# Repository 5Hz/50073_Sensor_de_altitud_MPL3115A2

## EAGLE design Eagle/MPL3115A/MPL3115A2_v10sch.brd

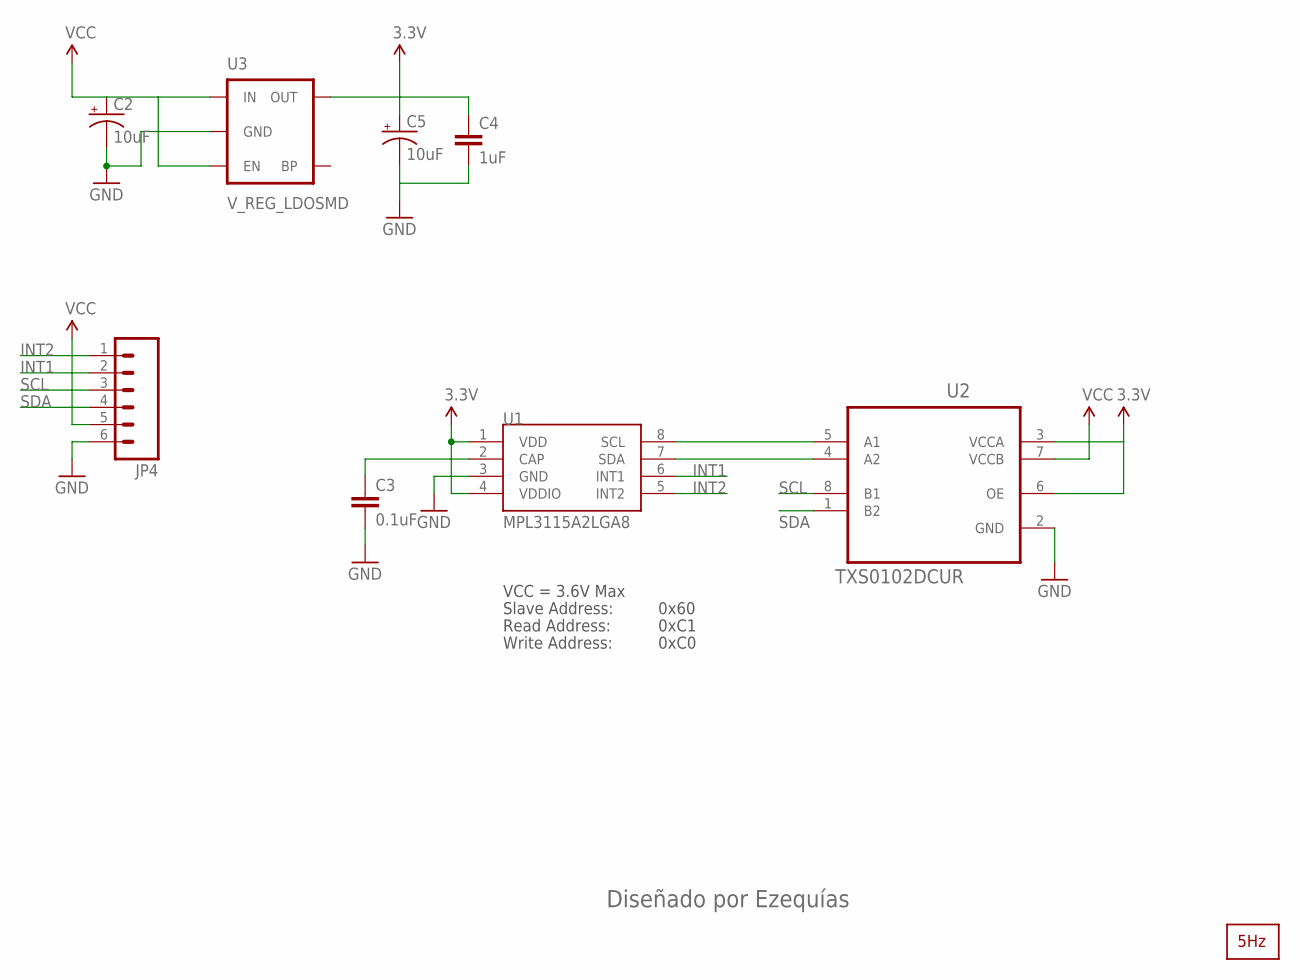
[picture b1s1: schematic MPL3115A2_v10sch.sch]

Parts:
C2, C5: 10uF; EIA3216
C3: 0.1uF; 0402-CAP
C4: 1uF; 0402-CAP
JP4: M06SIP; 1X06
U1: MPL3115A2LGA8; LGA8
U2: TXS0102DCUR; SOP50P310X90-8N
U3: V_REG_LDOSMD; SOT23-5
U$2: LOGO2_SILK5MM; LOGO2_5MM

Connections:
3.3V: C4.1, C5.A (+), U1.1 (VDD), U1.4 (VDDIO), U2.3 (VCCA), U2.6 (OE), U3.5 (OUT)
GND: C2.C (-), C3.2, C4.2, C5.C (-), JP4.6, U1.3 (GND), U2.2 (GND), U3.2 (GND)
INT1: JP4.2, U1.6 (INT1)
INT2: JP4.1, U1.5 (INT2)
unnamed: C3.1, U1.2 (CAP)
unnamed: U1.8 (SCL), U2.5 (A1)
unnamed: U1.7 (SDA), U2.4 (A2)
SCL: JP4.3, U2.8 (B1)
SDA: JP4.4, U2.1 (B2)
VCC: C2.A (+), JP4.5, U2.7 (VCCB), U3.1 (IN), U3.3 (EN)

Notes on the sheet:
VCC = 3.6V Max
Read Address:
Write Address:
Slave Address:
0x60
0xC1
0xC0
Diseñado por Ezequías

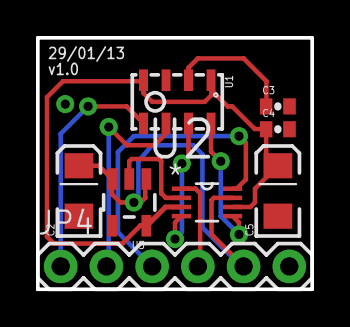
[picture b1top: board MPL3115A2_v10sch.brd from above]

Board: 2 copper layers, 15.2 x 14.0 mm, 9 parts (1 on the bottom side), 10 nets.

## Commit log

2014-01-13 creación

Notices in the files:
parts and their libraries:
SparkFun-Sensors: Licensing: CC v3.0 Share-Alike You are welcome to use this library for commercial purposes.
